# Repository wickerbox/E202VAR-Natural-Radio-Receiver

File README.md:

## Introduction

This project is based on the Explorer E202, with permission. 

Renato Romero put plans online for a Very Low Frequency (VLF) receiver capable between "a few Hz to beyond 10 kHz [which] makes it suitable to to receive radio signals of natural origin; signals not generated by human activity but by physical phenomena such as lightning and solar storms. Received signals are heard directly in your headset. The receiver amplifies the electric component of an electromagnetic signal."

His plans are <a href="http://www.vlf.it/romero2/explorer-e202.html">described on the vlf.it website</a>. The Explorer E202 is no longer available for sale.

He gave me permission to work from his schematic to design a new layout and make my own units. I am releasing all of my documents and process under the CERN Open Hardware License v1.2.

This is the original E202 full-size schematic.

\pagebreak

## Assembled v1.1 Receiver with Case

A fully assembled v1.1 in a box looked like this:

\pagebreak

## Assembled v1.4 Receiver Board

The final board for v1.4, which is the release version, looks like this: 

\pagebreak

## Cost

Total cost of parts is about $25 if you order minimums. It's about $100 if you go to the next price break for most at qty=10, which is what I did since I'm prototyping, and what I recommend if you want to build two or more units. 

OSH Park: $35.35 for a set of three bare boards [<a href="https://oshpark.com/shared_projects/NvQSoarW">Shared Project #NvQSoarW</a>]

Digikey cart: $24.40 for parts for one board [<a href="http://www.digikey.com/short/32fqdm">Shared Cart #32fqdm</a>]

<!--- bom start --->
## Bill of Materials

|Ref|Qty|Description|Digikey PN|
|---|---|-----------|------|
|BNC1 BNC2 BNC3|3|CONN BNC JACK R/A 50 OHM PCB|A97555-ND|
|C1|1|CAP CER 0.033UF 50V C0G RADIAL|445-8490-ND|
|C10|1|CAP CER 10000PF 50V C0G RADIAL|445-8384-ND|
|C15 C14|2|CAP CER 0.022UF 50V X7R RADIAL|399-14089-1-ND|
|C16 C7|2|CAP CER 4700PF 50V C0G RADIAL|445-8585-ND|
|C2 C11|2|CAP CER 0.1UF 50V C0G RADIAL|445-8532-ND|
|C3|1|CAP CER 8.2PF 50V NP0 RADIAL|399-8923-ND|
|C5|1|CAP CER 150PF 50V NP0 RADIAL|BC1015CT-ND|
|C6 C12 C4|3|CAP CER 10UF 16V X5R RADIAL|445-8290-ND|
|C9 C13|2|CAP CER 100UF 6.3V X5R RADIAL|445-8441-ND|
|D1 D2|2|DIODE GEN PURP 50V 1A DO41|1N4001-TPMSCT-ND|
|D3|1|LED BLUE CLEAR 5MM ROUND T/H|C503B-BCS-CV0Z0461-ND|
|J1 J4|2|CONN PWR JACK 2.5X5.5MM HIGH CUR|PJ-202BH|
|J2 J5|2|CONN TERM SCREW GREEN 2.54MM 2POS TH|ED10561-ND|
|J3|1|CONN JACK STEREO R/A 3PIN 3.5MM|CP1-3523N-ND|
|L1|1|FIXED IND 3.3UH 575MA 300 MOHM|78F3R3J-RC-ND|
|LAMP1|1|LAMP NEON 6.2MM WIRE TERMINAL|A9A-ND|
|Q1 Q2|2|TRANS NPN 45V 0.1A TO-92|BC547BTACT-ND|
|R10|1|POT 10K OHM 1/5W PLASTIC LINEAR|987-1301-ND|
|R11|1|RES 4.7K OHM 1/4W 5% CF MINI|S4.7KQCT-ND|
|R12|1|RES 2.2K OHM 1/4W 5% CARBON FILM|CF14JT2K20CT-ND|
|R13|1|RES 1K OHM 1/4W 5% CF MINI|S1KQCT-ND|
|R4|1|RES 3.3K OHM 1/4W 5% CARBON FILM|CF14JT3K30CT-ND|
|R5 R1|2|RES 10M OHM 1/4W 5% CARBON FILM|CF14JT10M0CT-ND|
|R6 R2 R3|3|RES 100K OHM 1/4W 5% CARBON FILM|CF14JT100KCT-ND|
|R7|1|RES 10 OHM 1/4W 5% CARBON FILM|CF14JT10R0CT-ND|
|R8|1|RES 10K OHM 1/4W 5% CF MINI|S10KQCT-ND|
|R9 R17|2|RES 33 OHM 1/4W 5% CARBON FILM|CF14JT33R0CT-ND|
|U1|1|IC REG LDO 9V 1A MC7809 TO220AB|MC7809CTGOS-ND|
|U2|1|IC VREF GND REF ADJ TO92|296-6549-5-ND|
|U3|1|IC AUDIO PWR AMP LOW VOLT 8-DIP|NJM386D-ND|
|U4|1|IC OPAMP JFET 3MHZ DIP8|296-7203-5-ND|

<!--- bom end --->

\pagebreak

## Gerber Preview

\pagebreak

## Assembly Diagram

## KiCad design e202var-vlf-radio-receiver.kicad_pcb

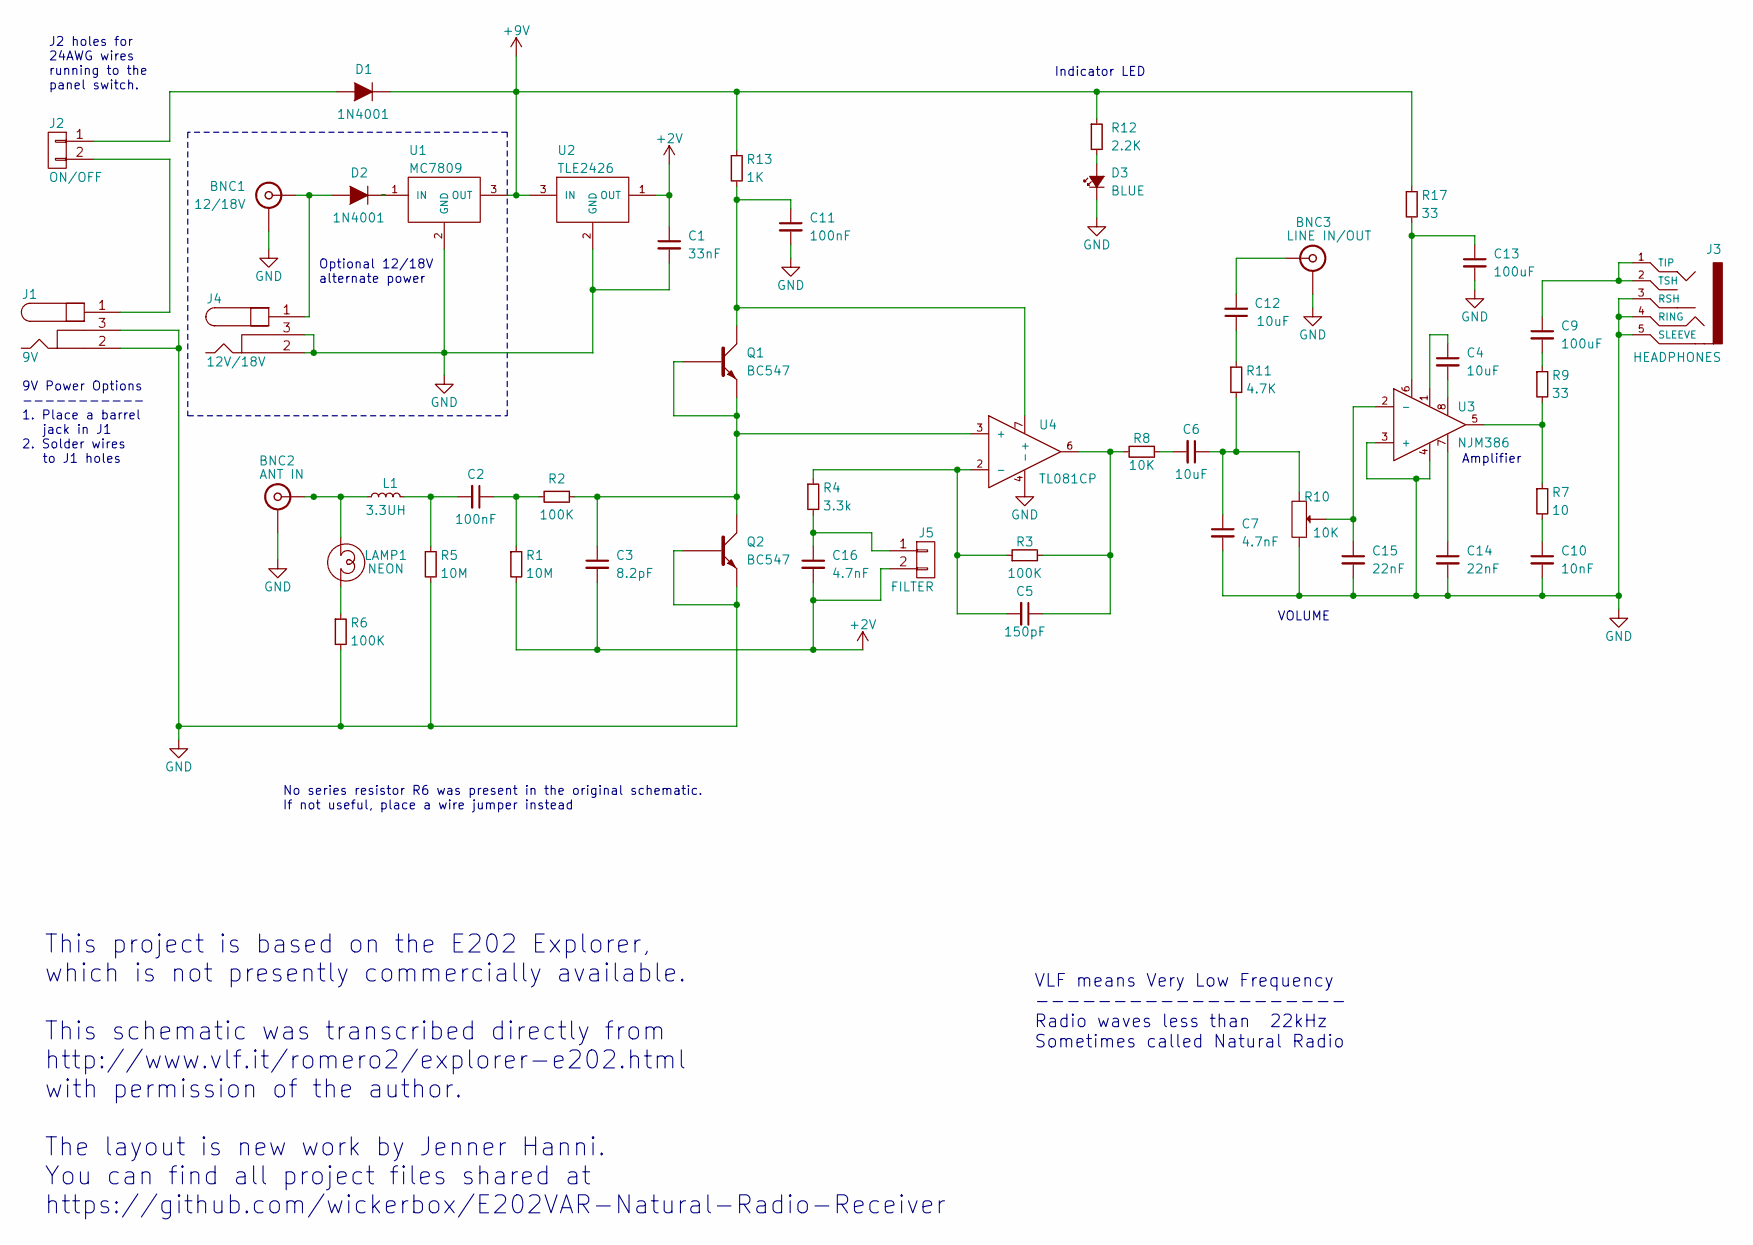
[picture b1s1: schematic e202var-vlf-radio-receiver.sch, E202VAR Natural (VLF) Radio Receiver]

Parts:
BNC1: 12/18V; CONN-BNC-TECONN-1-1634612-0
BNC2: ANT IN; CONN-BNC-TECONN-1-1634612-0
BNC3: LINE IN/OUT; CONN-BNC-TECONN-1-1634612-0
C1: 33nF; CAP-DISC-D7.5MM-P5MM
C2, C11: 100nF; CAP-DISC-D7.5MM-P5MM
C3: 8.2pF; CAP-DISC-D7.5MM-P5MM
C4, C6, C12: 10uF; CAP-DISC-D3MM-P2.5MM
C5: 150pF; CAP-DISC-D3MM-P2.5MM
C7, C16: 4.7nF; CAP-DISC-D7.5MM-P5MM
C9, C13: 100uF; CAP-DISC-D7.5MM-P5MM
C10: 10nF; CAP-DISC-D3MM-P2.5MM
C14, C15: 22nF; CAP-DISC-D3MM-P2.5MM
D1, D2: 1N4001; DIODE-DO-41
D3: BLUE; LED-D5MM-2PIN
J1: 9V; CONN-BARREL-JACK-2.5x5.5MM-TH
J2: ON/OFF; CONN-ONSHORE-SCREW-GREEN-2PIN-TH
J3: HEADPHONES; SJ1-3523N
J4: 12V/18V; CONN-BARREL-JACK-2.5x5.5MM-TH
J5: FILTER; CONN-ONSHORE-SCREW-GREEN-2PIN-TH
L1: 3.3UH; RES-CARBONFILM-7MM
LAMP1: NEON; CONN-HEADER-STRAIGHT-P2.54MM-1x02
Q1, Q2: BC547; TO-92-INLINE-NARROW-OVAL
R1, R5: 10M; RES-CARBONFILM-7MM
R2, R3, R6: 100K; RES-CARBONFILM-7MM
R4: 3.3k; RES-CARBONFILM-7MM
R7: 10; RES-CARBONFILM-7MM
R8: 10K; RES-CARBONFILM-7MM
R9, R17: 33; RES-CARBONFILM-7MM
R10: 10K; RES-TRIMPOT-TTELEC-P160-TH
R11: 4.7K; RES-CARBONFILM-7MM
R12: 2.2K; RES-CARBONFILM-7MM
R13: 1K; RES-CARBONFILM-7MM
U1: MC7809; TO-220-NEUTRAL123-HORZ-LONGPADS
U2: TLE2426; TO-92-INLINE-NARROW-OVAL
U3: NJM386; DIP-8-W7.62MM-LONGPADS
U4: TL081CP; DIP-8-W7.62MM-LONGPADS

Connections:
+2V: C1.1, C3.2, C16.2, J5.2, R1.2, U2.1 (OUT)
+9V: D1.1 (K), R12.1, R13.1, R17.1, U1.3 (OUT), U2.3 (IN)
GND: BNC1.2 (GND), BNC2.2 (GND), BNC3.2 (GND), C1.2, C7.2, C10.2, C11.2, C13.2, C14.2, C15.2, D3.1 (K), J1.2, J1.3, J3.3 (RSH), J3.4 (RING), J3.5 (SLEEVE), J4.2, J4.3, Q2.1 (B), Q2.2 (E), R5.2, R6.2, R10.3, U1.2 (GND), U2.2 (GND), U3.3 (+), U3.4, U4.4 (-)
unnamed: BNC1.1 (SIGNAL), D2.2 (A), J4.1
unnamed: BNC2.1 (SIGNAL), L1.1, LAMP1.1
unnamed: BNC3.1 (SIGNAL), C12.2
unnamed: C2.1, R1.1, R2.2
unnamed: C2.2, L1.2, R5.1
unnamed: C3.1, Q1.1 (B), Q1.2 (E), Q2.3 (C), R2.1, U4.3 (+)
unnamed: C4.1, U3.1
unnamed: C4.2, U3.8
unnamed: C5.1, R3.2, R8.2, U4.6
unnamed: C5.2, R3.1, R4.1, U4.2 (-)
unnamed: C6.1, C7.1, R10.1, R11.2
unnamed: C6.2, R8.1
unnamed: C9.1, J3.1 (TIP), J3.2 (TSH)
unnamed: C9.2, R9.1
unnamed: C10.1, R7.2
unnamed: C11.1, Q1.3 (C), R13.2, U4.7 (+)
unnamed: C12.1, R11.1
unnamed: C13.1, R17.2, U3.6
unnamed: C14.1, U3.7
unnamed: C15.1, R10.2, U3.2 (-)
unnamed: C16.1, J5.1, R4.2
unnamed: D1.2 (A), J2.1
unnamed: D2.1 (K), U1.1 (IN)
unnamed: D3.2 (A), R12.2
unnamed: J1.1, J2.2
unnamed: LAMP1.2, R6.1
unnamed: R7.1, R9.2, U3.5

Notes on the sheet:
J2 holes for 24AWG wires running to the panel switch.
Indicator LED
VOLUME
Optional 12/18V alternate power
9V Power Options ----------- 1. Place a barrel jack in J1 2. Solder wires to J1 holes
No series resistor R6 was present in the original schematic. If not useful, place a wire jumper instead
VLF means Very Low Frequency -------------------- Radio waves less than 22kHz Sometimes called Natural Radio
This project is based on the E202 Explorer, which is not presently commercially available. This schematic was transcribed directly from http://www.vlf.it/romero2/explorer-e202.html with permission of the author. The layout is new work by Jenner Hanni. You can find all project files shared at https: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
Amplifier

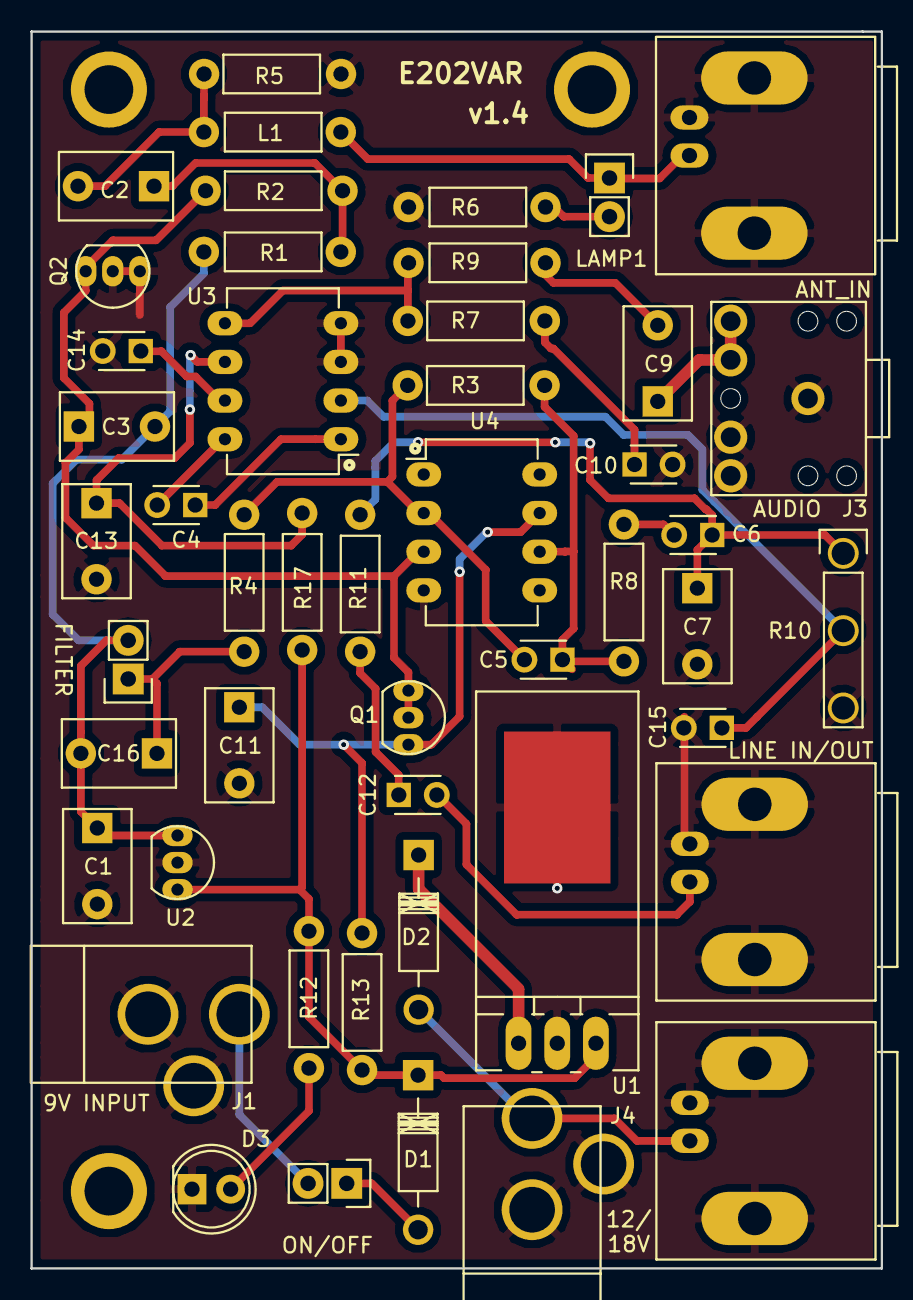
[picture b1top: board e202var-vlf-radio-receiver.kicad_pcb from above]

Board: 2 copper layers, 55.9 x 81.3 mm, 51 parts (0 on the bottom side), 30 nets.

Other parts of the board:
H1, H2, H3: HOLE-PLATED-3.2MM

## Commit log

2015-10-16 Added license.
2015-10-16 Added BOM.
2015-10-20 Added notes, clarified BOM a little.
2015-10-20 Finished first pass of schematic. Ready for review.
2015-10-24 Changed name. Cleaned up schematic. Added notes and exported BOM. Need to compare.
2015-10-24 Updated README.
2015-10-24 Added image to readme.
2015-10-24 Checking spaces in BOM.
2015-10-24 Finished capacitors and diodes.
2015-10-24 Tweaks!
2015-10-24 Added resistors.
2015-10-24 Parts selected! BOM created! (For now...)
2015-10-24 Cleaned up the notes. Final. Ready to merge.
2015-10-25 Changed R7 so all resistors are from same family.
2015-10-25 Changed R7, checked off verified BOM todo item.
2015-10-25 Changed LAMP(A) to a 4mm neon indicator. Added cost.
2015-10-25 Adding spot for R6 for testing. Possible DNP.
2015-10-25 Changed OP1 refdes to U4
2015-10-25 Added datasheets for most of the parts.
2015-10-25 Added e202var library and clean schematic.
2015-10-25 Made sure README and BOM.md agree on final BOM.
2015-10-25 Fixing the broken markdown table.
2015-10-25 Updated schematic PNG image from schematic.
2015-10-25 Added frame. Regenerated image.
2015-10-25 Placed components. Board size probably 2.22x3.18 inches. 5.25 for three at OSH Park.
2015-10-25 Finished layout.
2015-10-25 Added schematic, layout, and OSH Park preview images.
2015-10-25 Added CAM, DRU, clean BOM, library, and final of everything. Now we wait for Oct 30th.
2015-12-19 Version 1.1 draft, awaiting last round of testing.
2015-12-19 Getting the repo set up for v1.1
2015-12-19 Finished a sentence, added images.
2016-12-06 Created Kicad schematic for v1.1.
2016-12-09 Rough part placement. Created README. Images made by gerbv are off-center.
2016-12-10 Added parts. Ready for layout.
2016-12-10 Ported the board to KiCad.
2016-12-10 Release v1.2
2016-12-10 Clarified sections in README.
2016-12-10 Argh. typo.
2016-12-10 Cleanup
2016-12-26 v1.3 fixes in place. Saving before running script.
2016-12-26 Moved folders around.
2016-12-26 Playing with kingfisher.
2016-12-27 v1.3 release.
2016-12-27 Fix v1.3 PDF. Order boards.
2016-12-27 Added OSH Park link.
2017-02-23 Fixed several schematic issues.
2017-02-23 v1.4 because of silly schematic mistakes.
2017-02-24 Added three mounting holes to v1.4. Release.
2017-03-14 Release v1.4. Verified build. Project complete.
2017-03-15 Added v1.4 assembled image.

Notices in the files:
e202var-vlf-radio-receiver.sch:
Released under the CERN Open Hardware License v1.2
